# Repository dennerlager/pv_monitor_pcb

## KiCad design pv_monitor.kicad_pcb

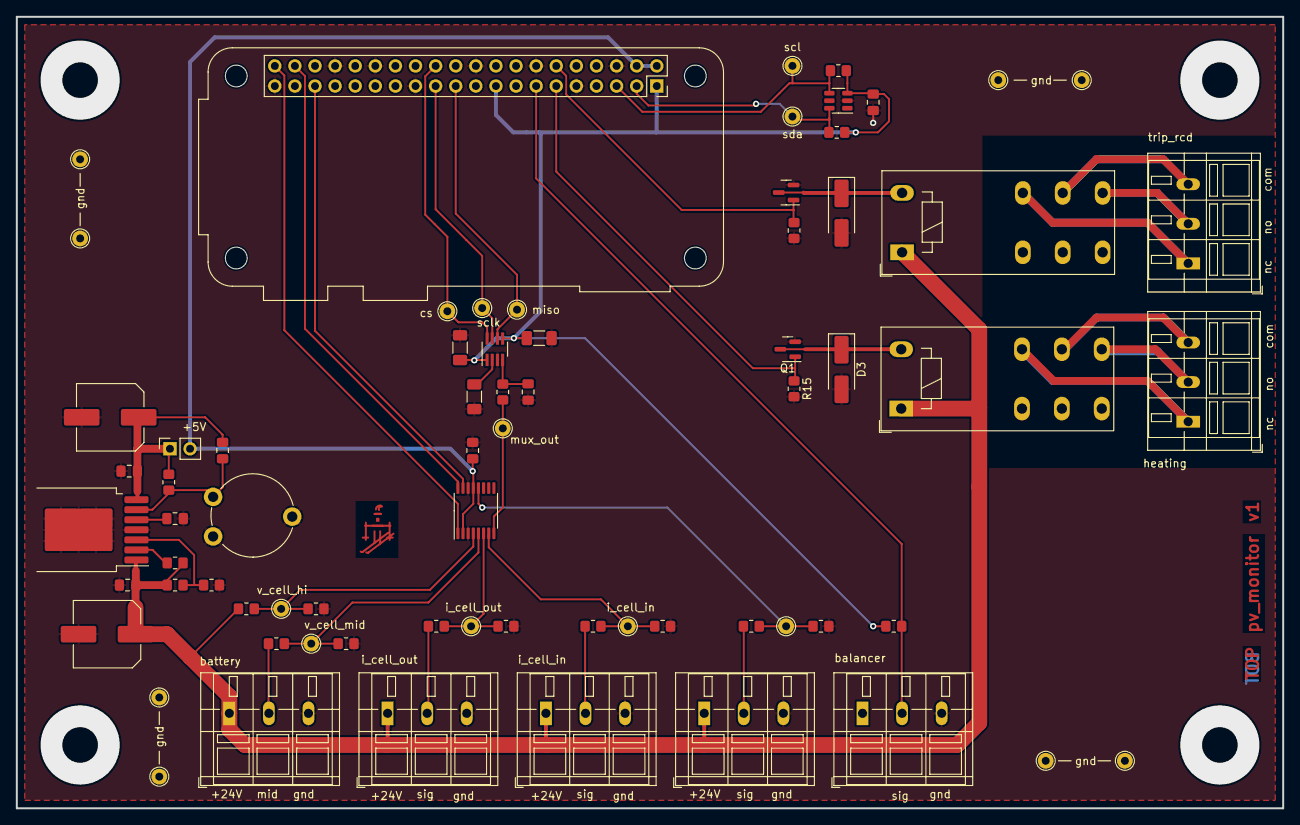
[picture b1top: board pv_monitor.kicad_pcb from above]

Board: 2 copper layers, 160.0 x 100.0 mm, 71 parts (0 on the bottom side), 40 nets.

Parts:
C1, C2, C6, C8, C9, C10, C12: 100n; C_0805_2012Metric_Pad1.18x1.45mm_HandSolder
C3, C4, C5: 2u2; C_1206_3216Metric_Pad1.33x1.80mm_HandSolder
C7, C11: 100u; C_Elec_8x10.2
D3, D4: SMAZ12-13-F; D_SMA_Handsoldering
J1: cell out current; TerminalBlock_WAGO_236-103_1x03_P5.00mm_45Degree
J2: cell in current; TerminalBlock_WAGO_236-103_1x03_P5.00mm_45Degree
J3: battery; TerminalBlock_WAGO_236-103_1x03_P5.00mm_45Degree
J4: spare; TerminalBlock_WAGO_236-103_1x03_P5.00mm_45Degree
J5: heating; TerminalBlock_WAGO_236-103_1x03_P5.00mm_45Degree
J6: balancer; TerminalBlock_WAGO_236-103_1x03_P5.00mm_45Degree
J7: Raspberry_Pi_2_3; Raspberry_Pi_Zero_Socketed_THT_FaceDown_MountingHoles
J8: trip_rcd; TerminalBlock_WAGO_236-103_1x03_P5.00mm_45Degree
JP1: PinSocket_1x02_P2.54mm_Vertical
K1, K2: RT424024; Relay_DPDT_Schrack-RT2-FormC_RM5mm
Q1, Q2: DMG3402L; SOT-23
R1, R3: 150k; R_0805_2012Metric_Pad1.20x1.40mm_HandSolder
R2, R4, R15, R16, R17, R18: 100k; R_0805_2012Metric_Pad1.20x1.40mm_HandSolder
R5: 47R; R_0805_2012Metric_Pad1.20x1.40mm_HandSolder
R6: 120k; R_0805_2012Metric_Pad1.20x1.40mm_HandSolder
R7: 20k; R_0805_2012Metric_Pad1.20x1.40mm_HandSolder
R8: 130k; R_0805_2012Metric_Pad1.20x1.40mm_HandSolder
R9, R14: 10k; R_0805_2012Metric_Pad1.20x1.40mm_HandSolder
R10, R11: R; R_0805_2012Metric_Pad1.20x1.40mm_HandSolder
R12, R13, R19: 4k7; R_0805_2012Metric_Pad1.20x1.40mm_HandSolder
R20: 15k; R_0805_2012Metric_Pad1.20x1.40mm_HandSolder
RV1: 1k; Potentiometer_Piher_PT-10-V10_Vertical
TP1, TP2, TP4, TP5, TP6, TP7, TP8, TP9, TP10, TP11: TestPoint; TestPoint_THTPad_D2.0mm_Drill1.0mm
TP3, TP12, TP13, TP14, TP15, TP16, TP17, TP18, TP19: TestPoint_THTPad_D2.0mm_Drill1.0mm
U1: SOT-23-8_Handsoldering
U2: TSSOP-16_4.4x5mm_P0.65mm
U3: LM73; SOT-23-6
U4: Texas_NDW-7_TabPin4

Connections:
+3V3: C4.1, C5.1, C6.1, J7.1 (3V3), J7.17 (3V3), R12.1, R13.1, R14.1, U1.1 (VDD), U1.5 (OVDD), U3.3 (V_{DD})
+5V: C1.1, J7.2 (5V), J7.4 (5V), JP1.2 (B), U2.2 (EN), U2.13 (VDD)
+24V: C7.1, C8.1, J1.1, J2.1, J3.1, J4.1, K1.A1, K2.A1, R8.1, R17.1, R18.1, U4.1 (VIN)
/balancer_alarm: J6.2, J7.13 (GPIO27), R14.2
/cs_b: J7.24 (~CE0/GPIO8), TP9.1, U1.8 (CONV)
/heating: J7.11 (GPIO17), Q1.1 (G), R15.1
/i_cell_in: R1.2, R2.1, TP1.1, U2.7 (S4)
/i_cell_out: R3.2, R4.1, TP2.1, U2.6 (S3)
/miso: J7.21 (MISO0/GPIO9), TP10.1, U1.6 (SDO)
/mux_addr_0: J7.40 (GPIO21/SCLK1), U2.1 (A0)
/mux_addr_1: J7.38 (GPIO20/MOSI1), U2.16 (A1)
/mux_addr_2: J7.35 (GPIO19/MISO1), U2.15 (A2)
/scl: J7.5 (SCL/GPIO3), R13.2, TP8.1, U3.4 (SMBCLK)
/sclk: J7.23 (SCLK0/GPIO11), TP11.1, U1.7 (SCK)
/sda: J7.3 (SDA/GPIO2), R12.2, TP7.1, U3.6 (SMBDAT)
/spare: R10.2, R11.1, TP6.1, U2.12 (S5)
/trip_rcd: J7.12 (GPIO18/PWM0), Q2.1 (G), R16.1
/v_cell_hi: R8.2, R9.1, TP5.1, U2.4 (S1)
/v_cell_mid: R6.2, R7.1, TP4.1, U2.5 (S2)
GND: C1.2, C2.2, C3.2, C4.2, C5.2, C6.2, C7.2, C8.2, C10.2, C11.2, C12.2, D3.2 (A), D4.2 (A), J1.3, J2.3, J3.3, J4.3, J6.3, J7.6 (GND), J7.9 (GND), J7.14 (GND), J7.20 (GND), J7.25 (GND), J7.30 (GND), J7.34 (GND), J7.39 (GND), Q1.2 (S), Q2.2 (S), R2.2, R4.2, R7.2, R9.2, R11.2, R15.2, R16.2, R20.2, RV1.1, RV1.2, TP12.1, TP13.1, TP14.1, TP15.1, TP16.1, TP17.1, TP18.1, TP19.1, U1.3 (GND), U2.3 (VSS), U2.14 (GND), U3.2 (GND), U4.4 (GND)
unnamed: D3.1 (K), K1.A2, Q1.3 (D)
unnamed: D4.1 (K), K2.A2, Q2.3 (D)
unnamed: J1.2, R1.1
unnamed: J2.2, R3.1
unnamed: J3.2, R6.1
unnamed: J4.2, R10.1
unnamed: J5.1, K1.22
unnamed: J5.2, K1.24
unnamed: J5.3, K1.21
unnamed: J8.1, K2.22
unnamed: J8.2, K2.24
unnamed: J8.3, K2.21
unnamed: C9.1, C10.1, C11.1, JP1.1 (A), R19.1, U4.7 (VOUT)
unnamed: C2.1, R5.2, U1.4 (AIN)
unnamed: C3.1, U1.2 (VREF)
unnamed: R5.1, TP3.1, U2.8 (D)
unnamed: R17.2, R20.1, U4.3 (EN)
unnamed: C9.2, R19.2, RV1.3, U4.6 (FB)
unnamed: R18.2, U4.2 (RON)
unnamed: C12.1, U4.5 (SS)

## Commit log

2023-08-08 initial commit, schematic pretty much ready
2023-08-27 1st revision ready to order
